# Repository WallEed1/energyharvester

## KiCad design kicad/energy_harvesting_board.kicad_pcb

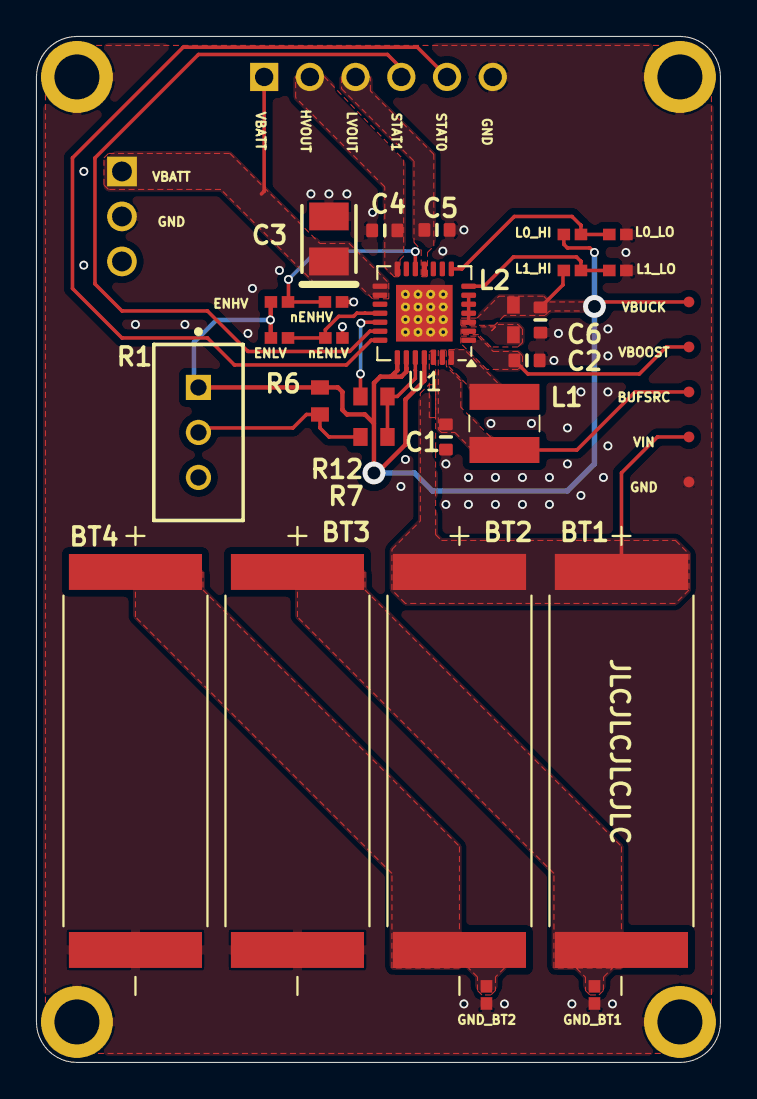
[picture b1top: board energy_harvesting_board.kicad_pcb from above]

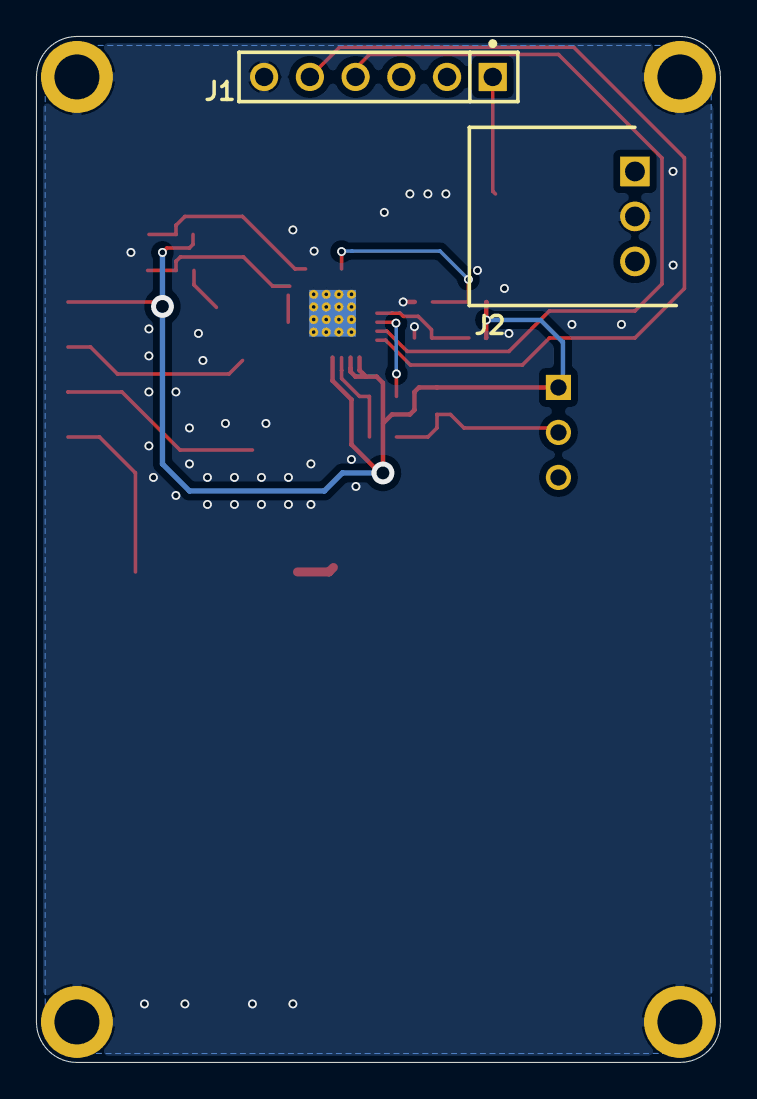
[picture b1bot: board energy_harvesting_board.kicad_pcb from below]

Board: 2 copper layers, 38.0 x 57.0 mm, 34 parts (2 on the bottom side), 21 nets.

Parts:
BT1, BT2, BT3, BT4: KXOB25-05X3F-TR; SOLAR_KXOB25-14X1F-TR
C1, C2, C4, C5, C6: Capacitor 10µF +/-20% 10V 0603; CAPC0603(1608)100_L
C3: TAJB106K016RNJ; AVX-TAJ-B-2_L
J1: 22-28-4063; FP-22-28-4063-MFG
J2: S3B-XH-A__LF__SN_; SHDRRA3W64P0X250_1X3_990X1150X610P
L1: 22µH; LPS4018223MRC
L2: 10µH; MURA-BLM18-F-H1-CHIP-2_V
R1: 100k POT; FP-PV36W-MFG
R2, R3, R4, R5, R8, R9, R10, R11, R13, R14: Resistor 0R 0402 63 mW; RESC1005X40X25ML05T10
R6, R7, R12: Resistor 0R +/- 5% 0603 100 mW; RESC1608X55X25ML10T15
TP1, TP2, TP3, TP4, TP5: TPAD6R; TP06R
U1: AEM00940; QFN-28-1EP_5x5mm_P0.5mm_EP3.1x3.1mm_ThermalVias

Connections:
ENHV: R4.1, R10.2, U1.12 (ENHV)
ENLV: R5.1, R11.2, U1.18 (ENLV)
GND: BT3.N, BT4.N, C1.2, C2.2, C3.2, C4.2, C5.1, C6.1, J1.6, J2.2, R8.1, R9.1, R10.1, R11.1, R13.2, R14.2, TP5.1, U1.9 (FB_PRIM_D), U1.10 (FB_PRIM_U), U1.17 (PRIM), U1.29 (GND)
HVOUT: C4.1, J1.2, U1.14 (HVOUT)
LVOUT: C5.2, J1.3, U1.11 (LVOUT)
NetBT1_N: BT1.N, BT3.P, R13.1
NetBT2_N: BT2.N, BT4.P, R14.1
NetC1_1: C1.1, L1.2, TP1.1, U1.27 (BUFSRC)
NetC2_1: C2.1, TP2.1, U1.1 (BOOST)
NetL1_1: L1.1, U1.28 (SWBOOST)
NetL2_1: L2.1, U1.2 (SWBUCK)
NetR1_2: R1.2, R6.1, R7.2
SRC_LVL_D: R12.1, U1.19 (SRC_LVL_D)
SRC_LVL_R0: R2.1, R8.2, U1.8 (SRC_LVL_RANGE[0])
SRC_LVL_R1: R3.1, R9.2, U1.7 (SRC_LVL_RANGE[1])
SRC_LVL_U: R7.1, R12.2, U1.24 (SRC_LVL_U)
STATUS0: J1.5, U1.21 (STATUS[0])
STATUS1: J1.4, U1.20 (STATUS[1])
VBATT: C3.1, J1.1, J2.1, U1.15 (BAL), U1.16 (BATT)
VBUCK: C6.2, L2.2, R1.1, R2.2, R3.2, R4.2, R5.2, R6.2, TP3.1, U1.3 (BUCK), U1.4 (CFG[2]), U1.5 (CFG[1]), U1.6 (CFG[0]), U1.22 (SET_OVCH), U1.23 (SET_CHRDY), U1.25 (SET_OVDIS)
V_IN: BT1.P, BT2.P, TP4.1, U1.26 (SRC)

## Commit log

2025-04-18 schematic aem
2025-05-15 "aem"
2025-05-17 added BT footprint and symbol
2025-05-19 layout 85
2025-05-19 layout v1
2025-06-09 v1.1 AEM00940 bard
